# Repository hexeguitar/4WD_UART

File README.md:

# 4WD UART
### CH344Q based quad isolated USB-UART interface with ESP programmer. 
![alt text][main_pic] 
### Features | Specs 
* 4 fully isolated channels  
  * Channel 0 - 2: classic UART with TX, RX, DTR and RTS signals
  * Channel 3: UART + ESP8266/ESP32 programmer signals (EN + IO0) and isolated 3.3V supply  
* individual TX/RX activity indicators per channel  
* theoretical max baud rate per channel: 6Mbps (tested up to 4.5Mbps on Linux)
* target voltage range: 3V - 5V (required for the isolators)
* USB C for power and data
* optional soft power switch (hold to power on/off) or regular toggle one
* USB inrush current limiter

<table>
  <tr>
    <td> </td>
    <td> </td>
  </tr>
  <tr>
    <td> </td>
    <td> </td>
  </tr>  
</table>  

### Leds  
Per channel:
* TX, RX - activity leds
* VTG - target power presence  

For channel 3:
* 3V3 - internal isolated 3.3V supply enable  

Global:
* TX, RX - global CH344Q activity leds
* ACT - USB enumeration success
* PWR - power indicator

### Electronic design  
![alt text][schematic] 
![alt text][pcb] 

### Mechanical design  
PCB is designed to slide into an 88x100x38mm aluminium extruded enclosure. Front panel and back panel PCBs replace the original plates.  
![alt text][mech1] 
![alt text][mech2] 

### Front panel  
Front panel is designed to accommodate the version with soft power switch. A normal pushbutton is used, but installed in reverse with terminals bent, as shown on the pic:  
![alt text][panel1]  
A single 1x02 0.1" SMD type pin header is used to connect the pushbutton to the main board.  
Light pipes for the leds can be made by pushing a tiny bit of hot glue into the holes.  

### Operation  
For most modern operating systems the device does not require any special drivers and should be detected automatically.  
On Linux 4WD UART is reporting as 4 /dev/TTYACMx devices:  
![alt text][linux]  

___
## All channels except 3 (if 3V3 is enabled) require external power supply in range from 3V to 5V to operate the output digital isolators and do the level shifting.  

Copyright (c) 2022 by Piotr Zapart  
www.hexefx.com  

## License
![alt text][cc-by-sa-image]  
This work is licensed under a [Creative Commons Attribution-ShareAlike 3.0 International License][cc-by-sa].  

[cc-by-sa]: http://creativecommons.org/licenses/by-sa/3.0/
[cc-by-sa-image]: https://licensebuttons.net/l/by-sa/3.0/88x31.png
[cc-by-sa-shield]: https://img.shields.io/badge/License-CC%20BY--SA%203.0-lightgrey.svg

[main_pic]: pics/4WD_UART_21.jpg "4WD UART front view"
[rear_view]: pics/4WD_UART_20.jpg "rear view"
[iso_view]: pics/4WD_UART_23.jpg "4WD UART"
[schematic]: MainBoard/4WD_UART_schm.png "4WD UART schematic"
[pcb]: pics/4WD_UART_pcb_kicad.jpg "4WD UART pcb"
[mech1]: pics/4wd_uart_freecad.jpg "4WD UART enclosure"
[mech2]: pics/enclosure.jpg "4WD UART enclosure"
[panel1]: pics/4WD_UART_25.jpg "4WD UART enclosure"  
[linux]: pics/ch344q_linux.jpg "4WD UART enclosure"

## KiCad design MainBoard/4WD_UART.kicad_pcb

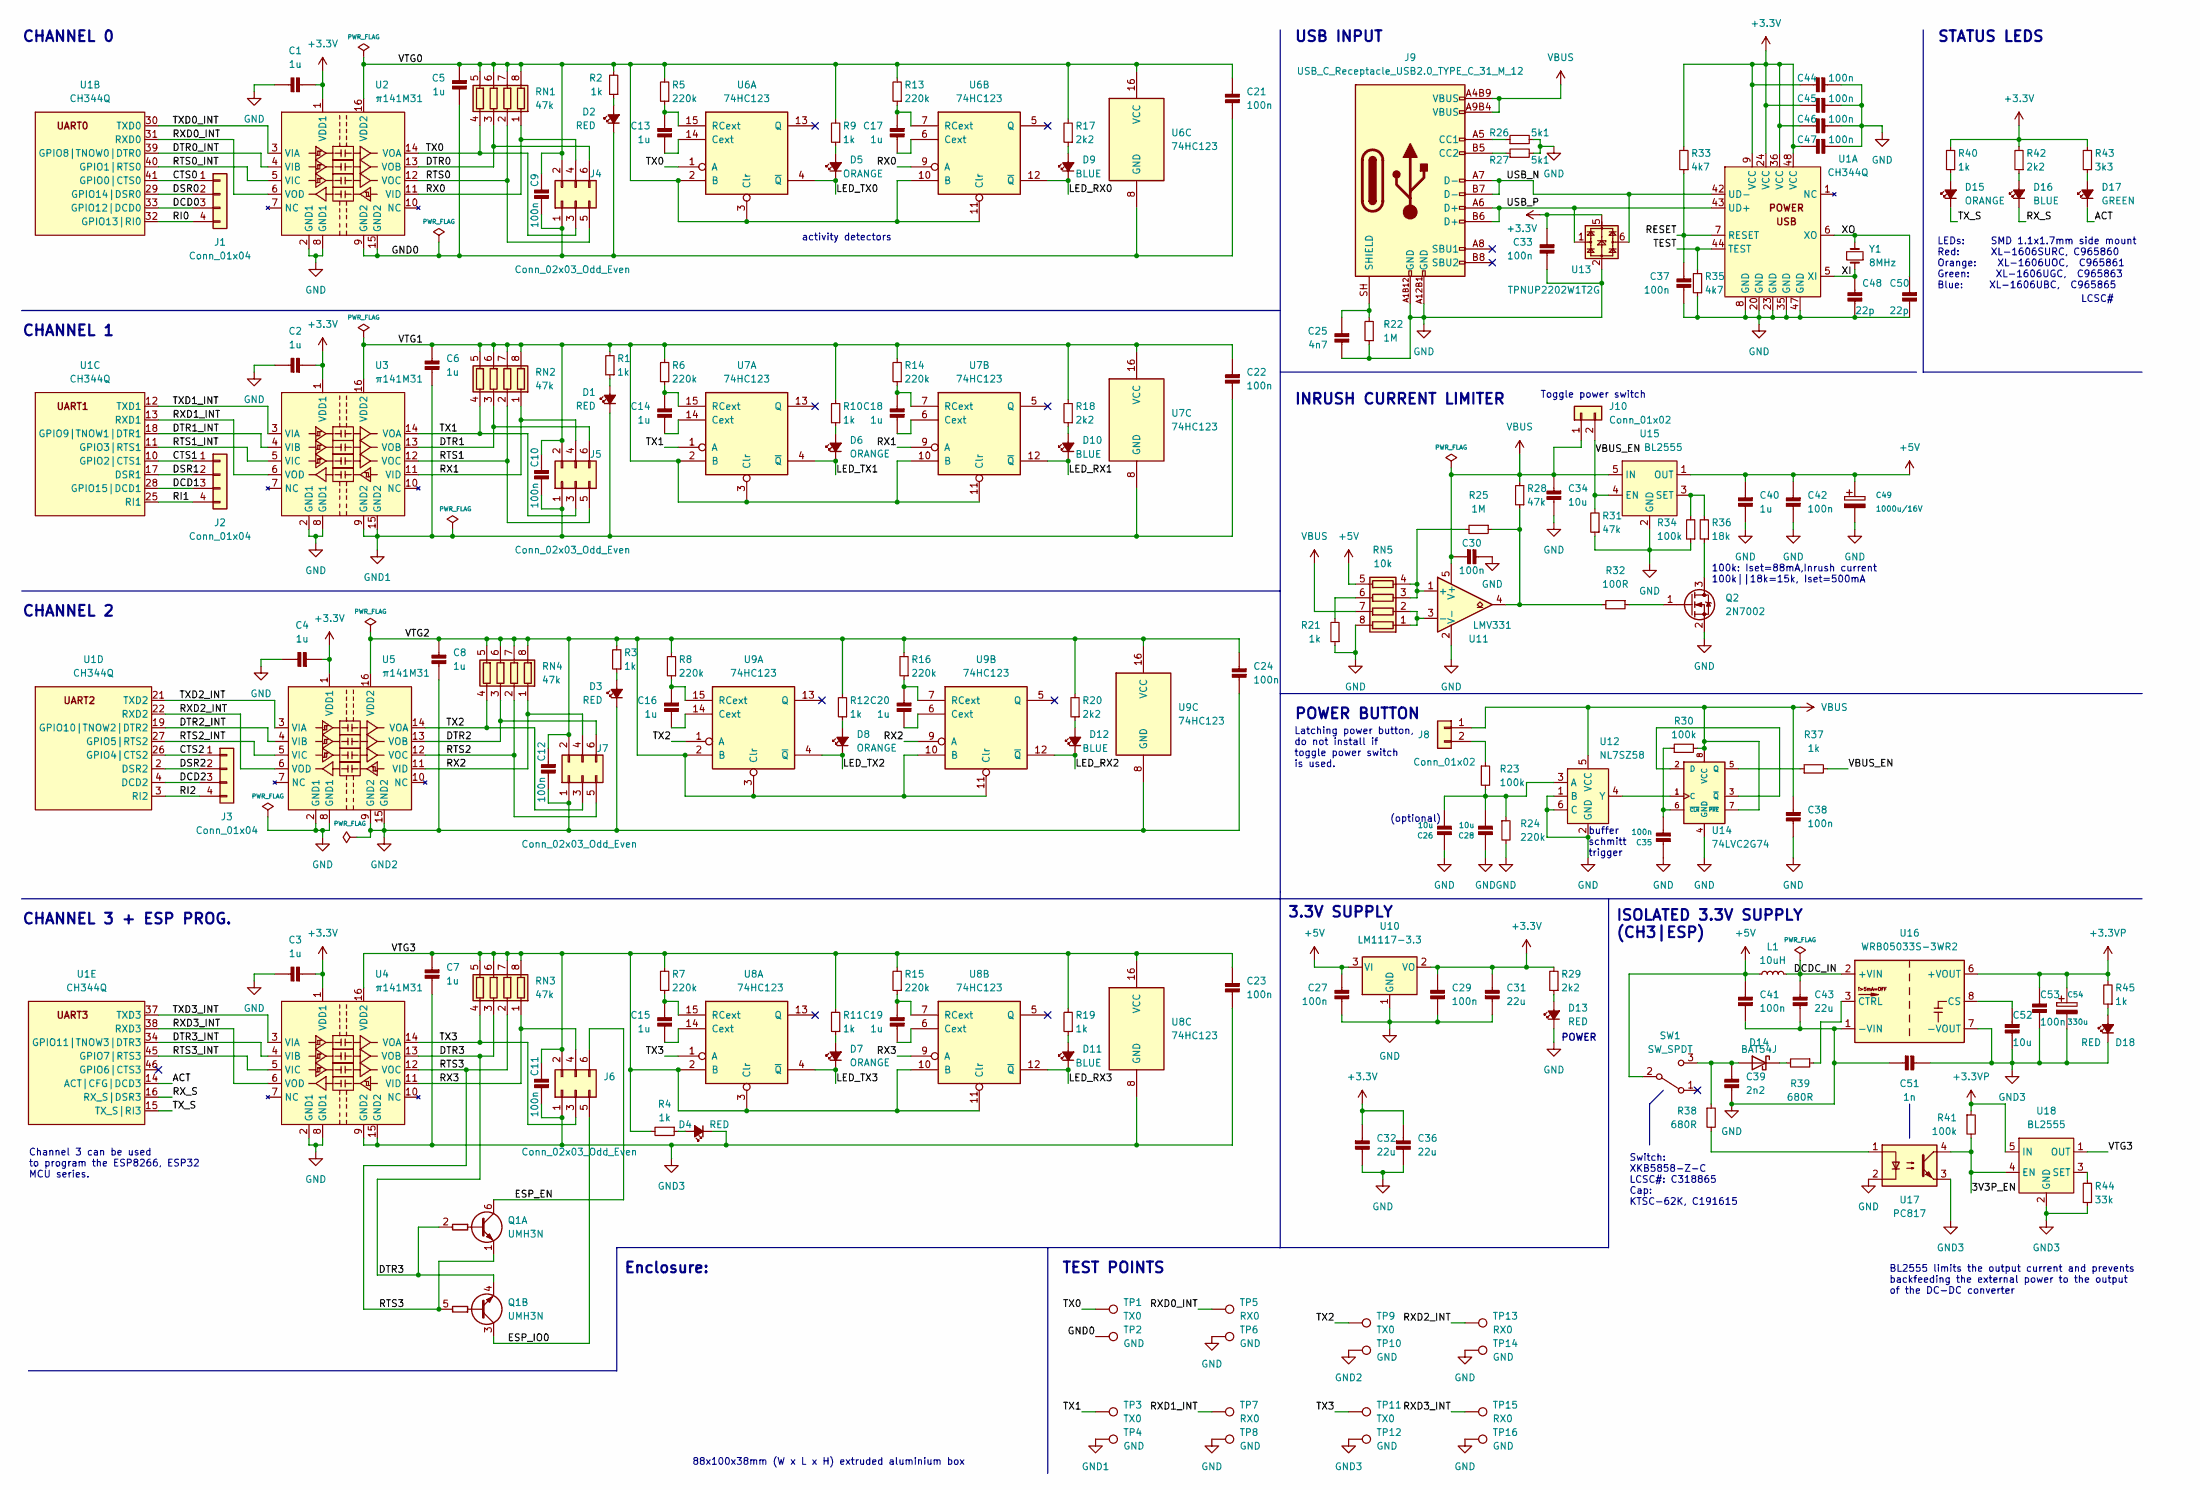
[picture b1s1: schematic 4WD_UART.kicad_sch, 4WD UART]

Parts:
C1, C2, C3, C4, C5, C6, C7, C8, C13, C14, C15, C16, C17, C18, C19, C20: 1u; Hx_C_0603_1608Metric
C9, C10, C11, C12, C35, C38, C41, C53: 100n; Hx_C_0805_2012Metric
C21, C22, C23, C24, C27, C29, C30, C33, C37, C42, C44, C45, C46, C47: 100n; Hx_C_0603_1608Metric
C25: 4n7; Hx_C_0805_2012Metric
C26, C28, C34, C52: 10u; Hx_C_0805_2012Metric
C31, C32, C36, C43: 22u; Hx_C_0805_2012Metric
C39: 2n2; Hx_C_0805_2012Metric
C40: 1u; Hx_C_0805_2012Metric
C48, C50: 22p; Hx_C_0805_2012Metric
C49: 1000u/16V; CP_Radial_D8.0mm_P3.50mm
C51: 1n; Hx_C_0805_2012Metric
C54: 330u; CP_Radial_D8.0mm_P3.50mm
D1, D2, D3, D4, D13, D18: RED; XL-1606_SMD side LED 1.7x1.1x0.6mm
D5, D6, D7, D8, D15: ORANGE; XL-1606_SMD side LED 1.7x1.1x0.6mm
D9, D10, D11, D12, D16: BLUE; XL-1606_SMD side LED 1.7x1.1x0.6mm
D14: BAT54J; D_SOD-323F
D17: GREEN; XL-1606_SMD side LED 1.7x1.1x0.6mm
J1, J2, J3: Conn_01x04; PinHeader_1x04_P2.54mm_Vertical
J4, J5, J6, J7: Conn_02x03_Odd_Even; IDC-Header_2x03_P2.54mm_Horizontal
J8, J10: Conn_01x02; JST_XA_B02B-XASK-1_1x02_P2.50mm_Vertical
J9: USB_C_Receptacle_USB2.0_TYPE_C_31_M_12; USB_C_TYPE-C-31-M-12; LCSC C283540
L1: 10uH; L_Coilcraft_LPS5030
Q1: UMH3N; SOT-363_SC-70-6
Q2: 2N7002; SOT-23
R1, R2, R3, R4, R9, R10, R11, R12, R19, R21, R37, R40, R45: 1k; Hx_R_0805_2012Metric
R5, R6, R7, R8, R13, R14, R15, R16, R24: 220k; Hx_R_0805_2012Metric
R17, R18, R20, R29, R42: 2k2; Hx_R_0805_2012Metric
R22, R25: 1M; Hx_R_0805_2012Metric
R23, R30, R34, R41: 100k; Hx_R_0805_2012Metric
R26, R27: 5k1; Hx_R_0805_2012Metric
R28, R31: 47k; Hx_R_0805_2012Metric
R32: 100R; Hx_R_0805_2012Metric
R33, R35: 4k7; Hx_R_0805_2012Metric
R36: 18k; Hx_R_0805_2012Metric
R38, R39: 680R; Hx_R_0805_2012Metric
R43: 3k3; Hx_R_0805_2012Metric
R44: 33k; Hx_R_0805_2012Metric
RN1, RN2, RN3, RN4: 47k; R_Array_Convex_4x0603
RN5: 10k; R_Array_Convex_4x0603
SW1: SW_SPDT; XKB5858-X-C_SPDT_PCB_angle_switch
TP1, TP3, TP9, TP11: TX0; TestPoint_THTPad_D1.5mm_Drill0.7mm
TP2, TP4, TP6, TP8, TP10, TP12, TP14, TP16: GND; TestPoint_THTPad_D1.5mm_Drill0.7mm
TP5, TP7, TP13, TP15: RX0; TestPoint_THTPad_D1.5mm_Drill0.7mm
U1: CH344Q; LQFP-48_7x7mm_P0.5mm; LCSC C2988084
U2, U3, U4, U5: π141M31; SOIC16; LCSC C471605
U6, U7, U8, U9: 74HC123; TSSOP-16_4.4x5mm_P0.65mm
U10: LM1117-3.3; SOT-223-3_TabPin2
U11: LMV331; SOT-23-5; LCSC C107643
U12: NL7SZ58; SOT-23-6
U13: TPNUP2202W1T2G; SOT-363_SC-70-6; LCSC C2959847
U14: 74LVC2G74; VSSOP-8_2.4x2.1mm_P0.5mm
U15, U18: BL2555; SOT-23-5; LCSC C2838883
U16: WRB05033S-3WR2; WRBD5xx5_3WR2
U17: PC817; DIP-4_W7.62mm
Y1: 8MHz; Crystal_HC49-U_Vertical

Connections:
+3.3VP: C53.2, C54.1, R41.1, R45.2, U16.6 (+VOUT), U18.5 (IN)
+3V3: C1.2, C2.2, C3.2, C4.2, C29.2, C31.2, C32.2, C33.2, C36.2, C44.2, C45.2, C46.2, C47.2, R29.2, R33.2, R40.2, R42.2, R43.2, U1.9 (VCC), U1.24 (VCC), U1.36 (VCC), U1.48 (VCC), U2.1 (VDD1), U3.1 (VDD1), U4.1 (VDD1), U5.1 (VDD1), U10.2 (VO), U13.5
+5V: C27.2, C40.2, C41.2, C42.2, C49.1, L1.1, RN5.5 (R4.2), SW1.2 (B), U10.3 (VI), U15.1 (OUT)
/3V3P_EN: R41.2, U17.4, U18.4 (EN)
/ACT: D17.1 (K), U1.14 (ACT|CFG|DCD3)
/CTS0: J1.1, U1.41 (GPIO0|CTS0)
/CTS1: J2.1, U1.10 (GPIO2|CTS1)
/CTS2: J3.1, U1.26 (GPIO4|CTS2)
/DCD0: J1.3, U1.33 (GPIO12|DCD0)
/DCD1: J2.3, U1.28 (GPIO15|DCD1)
/DCD2: J3.3, U1.4 (DCD2)
/DCDC_IN: C43.2, L1.2, U16.2 (+VIN)
/DSR0: J1.2, U1.29 (GPIO14|DSR0)
/DSR1: J2.2, U1.17 (DSR1)
/DSR2: J3.2, U1.2 (DSR2)
/DTR0: J4.6, RN1.3 (R3.1), U2.13 (VOB)
/DTR0_INT: U1.39 (GPIO8|TNOW0|DTR0), U2.4 (VIB)
/DTR1: J5.6, RN2.3 (R3.1), U3.13 (VOB)
/DTR1_INT: U1.18 (GPIO9|TNOW1|DTR1), U3.4 (VIB)
/DTR2: J7.6, RN4.3 (R3.1), U5.13 (VOB)
/DTR2_INT: U1.19 (GPIO10|TNOW2|DTR2), U5.4 (VIB)
/DTR3: Q1.2 (B1), Q1.4 (E2), RN3.3 (R3.1), U4.13 (VOB)
/DTR3_INT: U1.34 (GPIO11|TNOW3|DTR3), U4.4 (VIB)
/ESP_EN: J6.6, Q1.6 (C1)
/ESP_IO0: J6.5, Q1.3 (C2)
/GND0: C5.1, C9.1, C21.1, D2.1 (K), J4.1, TP2.1, U2.9 (GND2), U2.15 (GND2), U6.8 (GND)
/LED_RX0: D9.1 (K), U6.12 (~Q)
/LED_RX1: D10.1 (K), U7.12 (~Q)
/LED_RX2: D12.1 (K), U9.12 (~Q)
/LED_RX3: D11.1 (K), U8.12 (~Q)
/LED_TX0: D5.1 (K), U6.4 (~Q)
/LED_TX1: D6.1 (K), U7.4 (~Q)
/LED_TX2: D8.1 (K), U9.4 (~Q)
/LED_TX3: D7.1 (K), U8.4 (~Q)
/RESET: C37.2, R33.1, U1.7 (RESET)
/RI0: J1.4, U1.32 (GPIO13|RI0)
/RI1: J2.4, U1.25 (RI1)
/RI2: J3.4, U1.3 (RI2)
/RTS0: J4.5, RN1.2 (R2.1), U2.12 (VOC)
/RTS0_INT: U1.40 (GPIO1|RTS0), U2.5 (VIC)
/RTS1: J5.5, RN2.2 (R2.1), U3.12 (VOC)
/RTS1_INT: U1.11 (GPIO3|RTS1), U3.5 (VIC)
/RTS2: J7.5, RN4.2 (R2.1), U5.12 (VOC)
/RTS2_INT: U1.27 (GPIO5|RTS2), U5.5 (VIC)
/RTS3: Q1.1 (E1), Q1.5 (B2), RN3.2 (R2.1), U4.12 (VOC)
/RTS3_INT: U1.45 (GPIO7|RTS3), U4.5 (VIC)
/RX0: J4.4, RN1.1 (R1.1), U2.11 (VID), U6.9 (A)
/RX1: J5.4, RN2.1 (R1.1), U3.11 (VID), U7.9 (A)
/RX2: J7.4, RN4.1 (R1.1), U5.11 (VID), U9.9 (A)
/RX3: J6.4, RN3.1 (R1.1), U4.11 (VID), U8.9 (A)
/RXD0_INT: TP5.1, U1.31 (RXD0), U2.6 (VOD)
/RXD1_INT: TP7.1, U1.13 (RXD1), U3.6 (VOD)
/RXD2_INT: TP13.1, U1.22 (RXD2), U5.6 (VOD)
/RXD3_INT: TP15.1, U1.38 (RXD3), U4.6 (VOD)
/RX_S: D16.1 (K), U1.16 (RX_S|DSR3)
/TEST: R35.2, U1.44 (TEST)
/TX0: J4.3, RN1.4 (R4.1), TP1.1, U2.14 (VOA), U6.1 (A)
/TX1: J5.3, RN2.4 (R4.1), TP3.1, U3.14 (VOA), U7.1 (A)
/TX2: J7.3, RN4.4 (R4.1), TP9.1, U5.14 (VOA), U9.1 (A)
/TX3: J6.3, RN3.4 (R4.1), TP11.1, U4.14 (VOA), U8.1 (A)
/TXD0_INT: U1.30 (TXD0), U2.3 (VIA)
/TXD1_INT: U1.12 (TXD1), U3.3 (VIA)
/TXD2_INT: U1.21 (TXD2), U5.3 (VIA)
/TXD3_INT: U1.37 (TXD3), U4.3 (VIA)
/TX_S: D15.1 (K), U1.15 (TX_S|RI3)
/USB_N: J9.A7 (D-), J9.B7 (D-), U1.42 (UD-), U13.6
/USB_P: J9.A6 (D+), J9.B6 (D+), U1.43 (UD+), U13.1
/VBUS_EN: J10.2, R31.2, R37.2, U15.4 (EN)
/VTG0: C5.2, C9.2, C21.2, J4.2, R2.2, R5.2, R9.2, R13.2, R17.2, RN1.5 (R4.2), RN1.6 (R3.2), RN1.7 (R2.2), RN1.8 (R1.2), U2.16 (VDD2), U6.2 (B), U6.3 (Clr), U6.10 (B), U6.11 (Clr), U6.16 (VCC)
/VTG1: C6.2, C10.2, C22.2, J5.2, R1.2, R6.2, R10.2, R14.2, R18.2, RN2.5 (R4.2), RN2.6 (R3.2), RN2.7 (R2.2), RN2.8 (R1.2), U3.16 (VDD2), U7.2 (B), U7.3 (Clr), U7.10 (B), U7.11 (Clr), U7.16 (VCC)
/VTG2: C8.2, C12.2, C24.2, J7.2, R3.2, R8.2, R12.2, R16.2, R20.2, RN4.5 (R4.2), RN4.6 (R3.2), RN4.7 (R2.2), RN4.8 (R1.2), U5.16 (VDD2), U9.2 (B), U9.3 (Clr), U9.10 (B), U9.11 (Clr), U9.16 (VCC)
/VTG3: C7.2, C11.2, C23.2, J6.2, R4.2, R7.2, R11.2, R15.2, R19.2, RN3.5 (R4.2), RN3.6 (R3.2), RN3.7 (R2.2), RN3.8 (R1.2), U4.16 (VDD2), U8.2 (B), U8.3 (Clr), U8.10 (B), U8.11 (Clr), U8.16 (VCC), U18.1 (OUT)
/XI: C48.2, U1.5 (XI), Y1.1
/XO: C50.2, U1.6 (XO), Y1.2
GND: C1.1, C2.1, C3.1, C4.1, C25.1, C26.2, C27.1, C28.2, C29.1, C30.1, C31.1, C32.1, C33.1, C34.1, C35.2, C36.1, C37.1, C38.1, C39.1, C40.1, C41.1, C42.1, C43.1, C44.1, C45.1, C46.1, C47.1, C48.1, C49.2, C50.1, C51.2, D13.1 (K), J9.A1B12 (GND), J9.A12B1 (GND), Q2.2 (S), R21.1, R22.1, R24.2, R26.2, R27.2, R31.1, R34.1, R35.1, RN5.8 (R1.2), TP6.1, TP8.1, TP14.1, TP16.1, U1.8 (GND), U1.20 (GND), U1.23 (GND), U1.35 (GND), U1.47 (GND), U2.2 (GND1), U2.8 (GND1), U3.2 (GND1), U3.8 (GND1), U4.2 (GND1), U4.8 (GND1), U5.2 (GND1), U5.8 (GND1), U10.1 (GND), U11.2 (V-), U12.1 (B), U12.2 (GND), U12.6 (C), U13.2, U14.4 (GND), U15.2 (GND), U16.1 (-VIN), U17.2
GND1: C6.1, C10.1, C22.1, D1.1 (K), J5.1, TP4.1, U3.9 (GND2), U3.15 (GND2), U7.8 (GND)
GND2: C8.1, C12.1, C24.1, D3.1 (K), J7.1, TP10.1, U5.9 (GND2), U5.15 (GND2), U9.8 (GND)
GND3: C7.1, C11.1, C23.1, C51.1, C52.1, C53.1, C54.2, D4.1 (K), D18.1 (K), J6.1, R44.1, TP12.1, U4.9 (GND2), U4.15 (GND2), U8.8 (GND), U16.7 (-VOUT), U17.3, U18.2 (GND)
unnamed: C13.1, U6.14 (Cext)
unnamed: C13.2, R5.1, U6.15 (RCext)
unnamed: C14.1, U7.14 (Cext)
unnamed: C14.2, R6.1, U7.15 (RCext)
unnamed: C15.1, U8.14 (Cext)
unnamed: C15.2, R7.1, U8.15 (RCext)
unnamed: C16.1, U9.14 (Cext)
unnamed: C16.2, R8.1, U9.15 (RCext)
unnamed: C17.1, U6.6 (Cext)
unnamed: C17.2, R13.1, U6.7 (RCext)
unnamed: C18.1, U7.6 (Cext)
unnamed: C18.2, R14.1, U7.7 (RCext)
unnamed: C19.1, U8.6 (Cext)
unnamed: C19.2, R15.1, U8.7 (RCext)
unnamed: C20.1, U9.6 (Cext)
unnamed: C20.2, R16.1, U9.7 (RCext)
unnamed: C25.2, J9.SH (SHIELD), R22.2
unnamed: C26.1, C28.1, R23.2, R24.1, U12.3 (A)
unnamed: C35.1, R30.1, U14.6 (~CLR)
unnamed: C39.2, D14.2 (A), R38.1, SW1.3 (C)
unnamed: C52.2, U16.8 (CS)
unnamed: D1.2 (A), R1.1
unnamed: D2.2 (A), R2.1
unnamed: D3.2 (A), R3.1
unnamed: D4.2 (A), R4.1
unnamed: D5.2 (A), R9.1
unnamed: D6.2 (A), R10.1
unnamed: D7.2 (A), R11.1
unnamed: D8.2 (A), R12.1
unnamed: D9.2 (A), R17.1
unnamed: D10.2 (A), R18.1
unnamed: D11.2 (A), R19.1
unnamed: D12.2 (A), R20.1
unnamed: D13.2 (A), R29.1
unnamed: D14.1 (K), R39.2
unnamed: D15.2 (A), R40.1
unnamed: D16.2 (A), R42.1
unnamed: D17.2 (A), R43.1
unnamed: D18.2 (A), R45.1
unnamed: J8.2, R23.1
unnamed: J9.A5 (CC1), R26.1
unnamed: J9.B5 (CC2), R27.1
unnamed: Q2.1 (G), R32.1
unnamed: Q2.3 (D), R36.1
unnamed: R21.2, RN5.6 (R3.2)
unnamed: R25.1, R28.1, R32.2, U11.4
unnamed: R25.2, RN5.3 (R3.1), RN5.4 (R4.1), U11.1 (+)
unnamed: R34.2, R36.2, U15.3 (SET)
unnamed: R37.1, U14.5 (Q)
unnamed: R38.2, U17.1
unnamed: R39.1, U16.3 (CTRL)
unnamed: R44.2, U18.3 (SET)
unnamed: RN5.1 (R1.1), RN5.2 (R2.1), U11.3 (-)
unnamed: U12.4 (Y), U14.1 (C)
unnamed: U14.2 (D), U14.3 (~Q)
VBUS: C30.2, C34.2, C38.2, J8.1, J9.A4B9 (VBUS), J9.A9B4 (VBUS), J10.1, R28.2, R30.2, RN5.7 (R2.2), U11.5 (V+), U12.5 (VCC), U14.7 (~PRE), U14.8 (VCC), U15.5 (IN)

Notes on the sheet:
TEST POINTS
Latching power button, do not install if toggle power switch is used.
BL2555 limits the output current and prevents backfeeding the external power to the output of the DC-DC converter
buffer schmitt trigger
INRUSH CURRENT LIMITER
88x100x38mm (W x L x H) extruded aluminium box
POWER BUTTON
Switch: XKB5858-Z-C LCSC#: C318865 Cap: KTSC-62K, C191615
3.3V SUPPLY
(optional)
100k: Iset=88mA,Inrush current 100k||18k=15k, Iset=500mA
STATUS LEDS
CHANNEL 3 + ESP PROG.
CHANNEL 1
LCSC#
POWER
Toggle power switch
activity detectors
Channel 3 can be used to program the ESP8266, ESP32 MCU series.
Enclosure:
CHANNEL 2
LEDs: SMD 1.1x1.7mm side mount Red: XL-1606SURC, C965860 Orange: XL-1606UOC, C965861 Green: XL-1606UGC, C965863 Blue: XL-1606UBC, C965865
CHANNEL 0
ISOLATED 3.3V SUPPLY (CH3|ESP)
USB INPUT

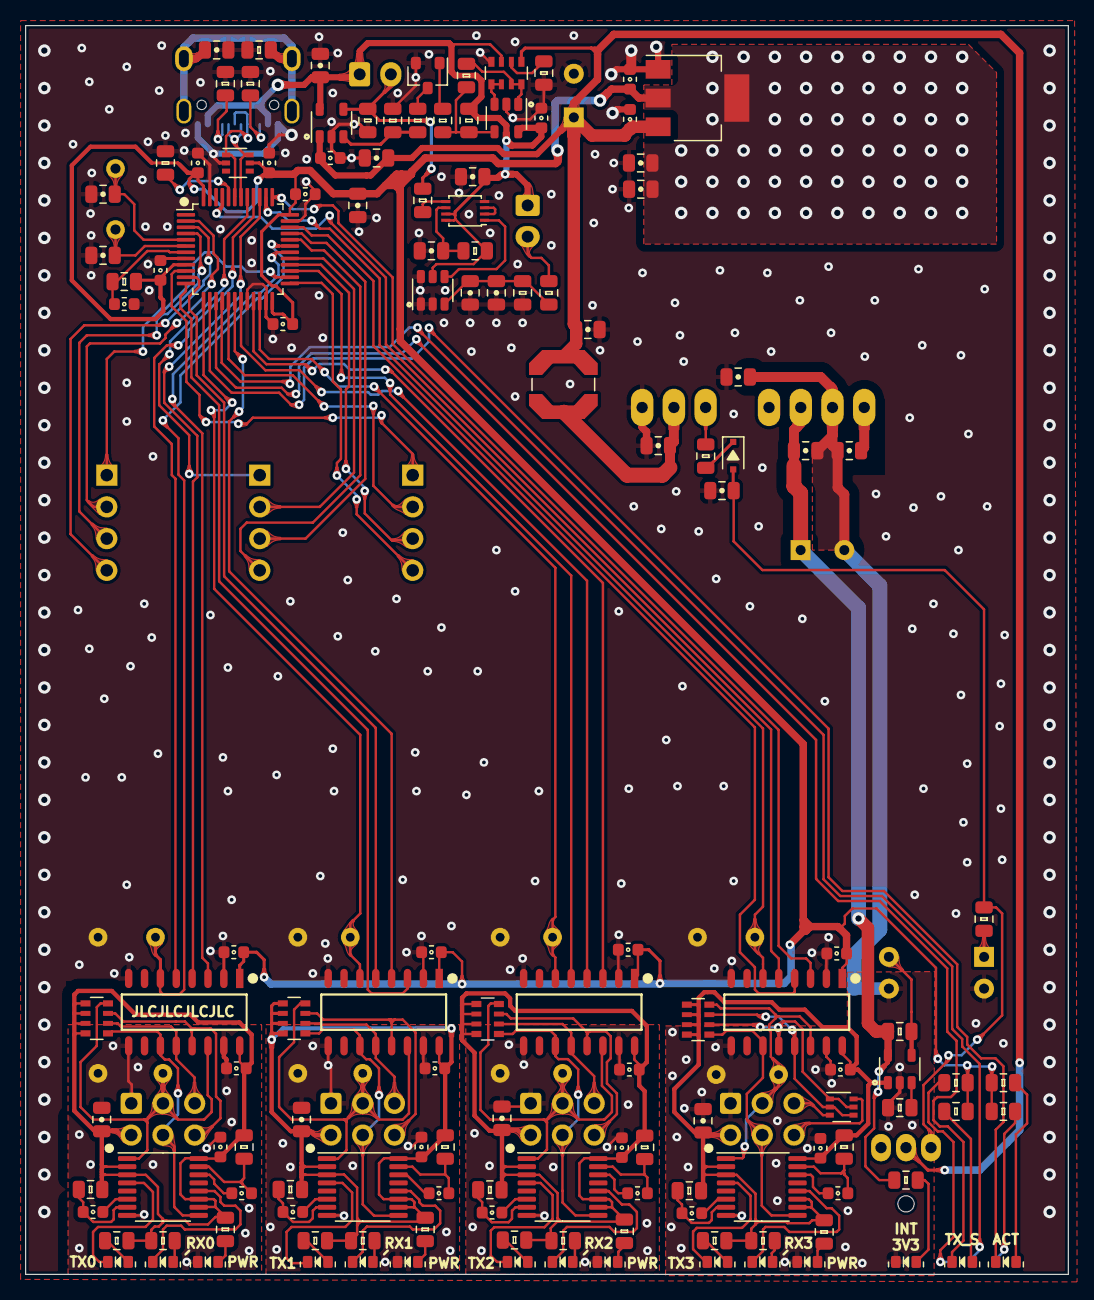
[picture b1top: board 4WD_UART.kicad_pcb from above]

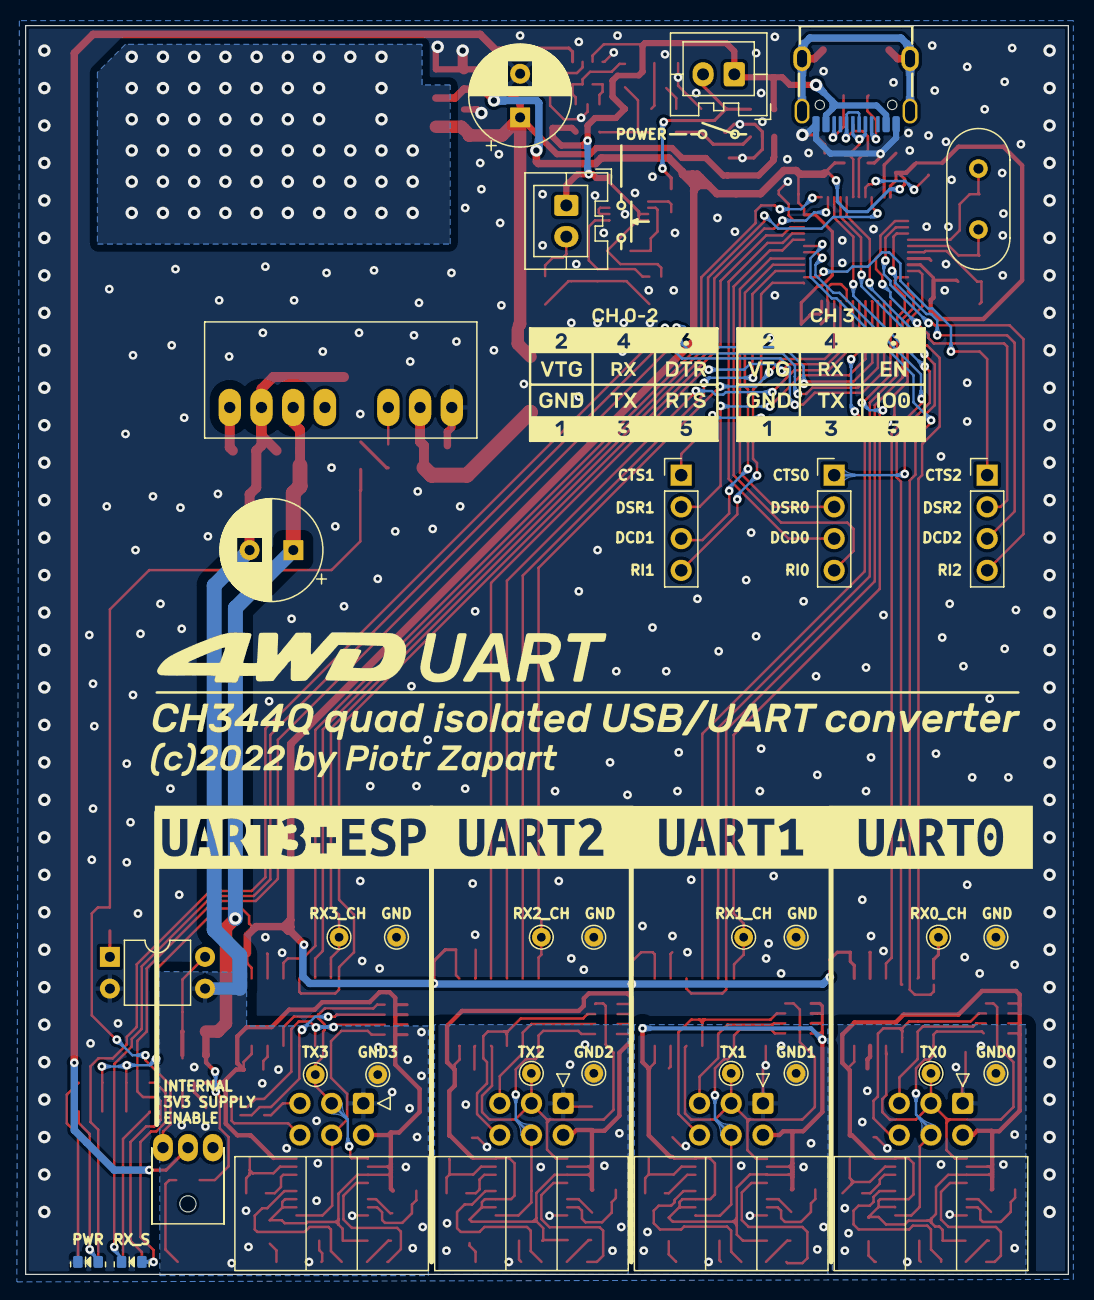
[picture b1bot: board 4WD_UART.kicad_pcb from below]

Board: 2 copper layers, 83.5 x 100.0 mm, 204 parts (67 on the bottom side), 134 nets.

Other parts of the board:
kibuzzard-62D9AA82: G***; kibuzzard-62D9AA82
kibuzzard-62D9AAED: G***; kibuzzard-62D9AAED
kibuzzard-62D9AB36: G***; kibuzzard-62D9AB36
kibuzzard-62D98D9A: G***; kibuzzard-62D98D9A
kibuzzard-62D98E0C: G***; kibuzzard-62D98E0C
kibuzzard-62D98E43: G***; kibuzzard-62D98E43
kibuzzard-62D98E49: G***; kibuzzard-62D98E49
kibuzzard-62DBE2B6, kibuzzard-62DBE2B6#2: G***; kibuzzard-62DBE2B6
kibuzzard-62DBE2BC, kibuzzard-62DBE2BC#2: G***; kibuzzard-62DBE2BC
kibuzzard-62DBE2C4, kibuzzard-62DBE2C4#2: G***; kibuzzard-62DBE2C4
kibuzzard-62DBE2D9: G***; kibuzzard-62DBE2D9
kibuzzard-62DBE2E2, kibuzzard-62DBE2E2#2: G***; kibuzzard-62DBE2E2
kibuzzard-62DBE4A6, kibuzzard-62DBE4A6#2: G***; kibuzzard-62DBE4A6
kibuzzard-62DBE6A2: G***; kibuzzard-62DBE6A2
kibuzzard-62DBE6B4: G***; kibuzzard-62DBE6B4
kibuzzard-62DBE386: G***; kibuzzard-62DBE386
kibuzzard-62DBE505, kibuzzard-62DBE505#2: G***; kibuzzard-62DBE505
kibuzzard-62DBE511, kibuzzard-62DBE511#2: G***; kibuzzard-62DBE511
kibuzzard-62DBE523, kibuzzard-62DBE523#2: G***; kibuzzard-62DBE523
kibuzzard-62DBE531, kibuzzard-62DBE531#2: G***; kibuzzard-62DBE531
kibuzzard-62DBE545, kibuzzard-62DBE545#2: G***; kibuzzard-62DBE545
kibuzzard-62DC16BA: G***; kibuzzard-62DC16BA
kibuzzard-62DC16CB: G***; kibuzzard-62DC16CB

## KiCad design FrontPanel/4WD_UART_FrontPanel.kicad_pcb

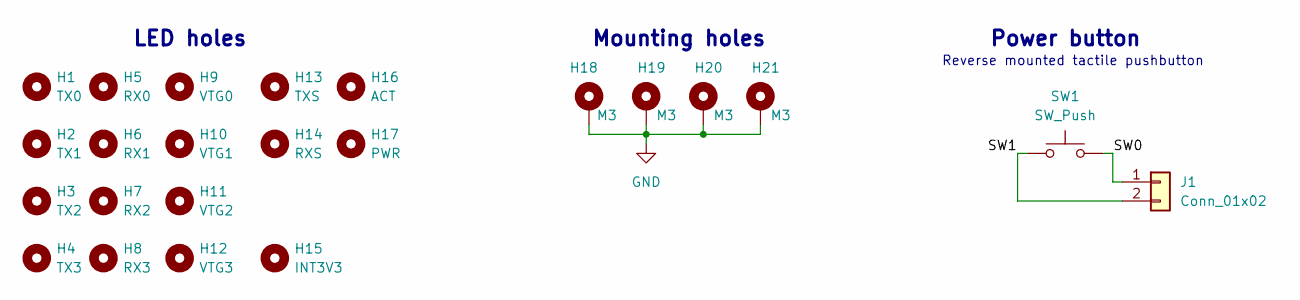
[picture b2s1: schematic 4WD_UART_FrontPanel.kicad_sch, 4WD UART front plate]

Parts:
H1: TX0; MountingHole_2.2mm_M2_ISO7380
H2: TX1; MountingHole_2.2mm_M2_ISO7380
H3: TX2; MountingHole_2.2mm_M2_ISO7380
H4: TX3; MountingHole_2.2mm_M2_ISO7380
H5: RX0; MountingHole_2.2mm_M2_ISO7380
H6: RX1; MountingHole_2.2mm_M2_ISO7380
H7: RX2; MountingHole_2.2mm_M2_ISO7380
H8: RX3; MountingHole_2.2mm_M2_ISO7380
H9: VTG0; MountingHole_2.2mm_M2_ISO7380
H10: VTG1; MountingHole_2.2mm_M2_ISO7380
H11: VTG2; MountingHole_2.2mm_M2_ISO7380
H12: VTG3; MountingHole_2.2mm_M2_ISO7380
H13: TXS; MountingHole_2.2mm_M2_ISO7380
H14: RXS; MountingHole_2.2mm_M2_ISO7380
H15: INT3V3; MountingHole_2.2mm_M2_ISO7380
H16: ACT; MountingHole_2.2mm_M2_ISO7380
H17: PWR; MountingHole_2.2mm_M2_ISO7380
H18, H19, H20, H21: M3; MountingHole_3.2mm_M3_Pad_Via
J1: Conn_01x02; PinHeader_1x02_P2.54mm_Vertical_SMD_Pin1Left
SW1: SW_Push; SW_Push_1P1T_NO_6x6mm_H9.5mm_reverse_mount

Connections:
/SW0: J1.1, SW1.2
/SW1: J1.2, SW1.1
GND: H18.1, H19.1, H20.1, H21.1

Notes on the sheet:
Reverse mounted tactile pushbutton
Mounting holes
LED holes
Power button

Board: 2 copper layers, 72 parts (2 on the bottom side), 3 nets, no tracks yet.

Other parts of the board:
kibuzzard-62D9AA82: G***; kibuzzard-62D9AA82
kibuzzard-62DBDE6B, kibuzzard-62DBDE6B#2, kibuzzard-62DBDE6B#3, kibuzzard-62DBDE6B#4: G***; kibuzzard-62DBDE6B
kibuzzard-62DBDE64: G***; kibuzzard-62DBDE64
kibuzzard-62DBE0FA: G***; kibuzzard-62DBE0FA
kibuzzard-62DBE1C8: G***; kibuzzard-62DBE1C8
kibuzzard-62DBE1D1: G***; kibuzzard-62DBE1D1
kibuzzard-62DBE1D8: G***; kibuzzard-62DBE1D8
kibuzzard-62DBE1FE: G***; kibuzzard-62DBE1FE
kibuzzard-62DBE2B6, kibuzzard-62DBE2B6#2: G***; kibuzzard-62DBE2B6
kibuzzard-62DBE2BC, kibuzzard-62DBE2BC#2: G***; kibuzzard-62DBE2BC
kibuzzard-62DBE2C4, kibuzzard-62DBE2C4#2: G***; kibuzzard-62DBE2C4
kibuzzard-62DBE2D9: G***; kibuzzard-62DBE2D9
kibuzzard-62DBE2E2, kibuzzard-62DBE2E2#2: G***; kibuzzard-62DBE2E2
kibuzzard-62DBE4A6, kibuzzard-62DBE4A6#2: G***; kibuzzard-62DBE4A6
kibuzzard-62DBE6A2: G***; kibuzzard-62DBE6A2
kibuzzard-62DBE6B4: G***; kibuzzard-62DBE6B4
kibuzzard-62DBE020: G***; kibuzzard-62DBE020
kibuzzard-62DBE071: G***; kibuzzard-62DBE071
kibuzzard-62DBE083: G***; kibuzzard-62DBE083
kibuzzard-62DBE135: G***; kibuzzard-62DBE135
kibuzzard-62DBE386: G***; kibuzzard-62DBE386
kibuzzard-62DBE505, kibuzzard-62DBE505#2: G***; kibuzzard-62DBE505
kibuzzard-62DBE511, kibuzzard-62DBE511#2: G***; kibuzzard-62DBE511
kibuzzard-62DBE523, kibuzzard-62DBE523#2: G***; kibuzzard-62DBE523
kibuzzard-62DBE531, kibuzzard-62DBE531#2: G***; kibuzzard-62DBE531
kibuzzard-62DBE545, kibuzzard-62DBE545#2: G***; kibuzzard-62DBE545
kibuzzard-62DBE989: G***; kibuzzard-62DBE989
kibuzzard-62DC0E3F: G***; kibuzzard-62DC0E3F
kibuzzard-62DC0E09: G***; kibuzzard-62DC0E09
kibuzzard-62DC0E10: G***; kibuzzard-62DC0E10
kibuzzard-62DC0E19: G***; kibuzzard-62DC0E19
kibuzzard-62DC0E21: G***; kibuzzard-62DC0E21
kibuzzard-62DC0E29: G***; kibuzzard-62DC0E29
kibuzzard-62DC0E32: G***; kibuzzard-62DC0E32
kibuzzard-62DC0E38: G***; kibuzzard-62DC0E38
kibuzzard-62DC0460: G***; kibuzzard-62DC0460

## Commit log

2022-09-14 design files added
2022-09-14 readme update
2022-09-15 datasheets added
2022-09-15 typo fix
2022-09-15 removed backups
2023-09-11 Convert to newer kicad version by saving in kicad-7.0.6
